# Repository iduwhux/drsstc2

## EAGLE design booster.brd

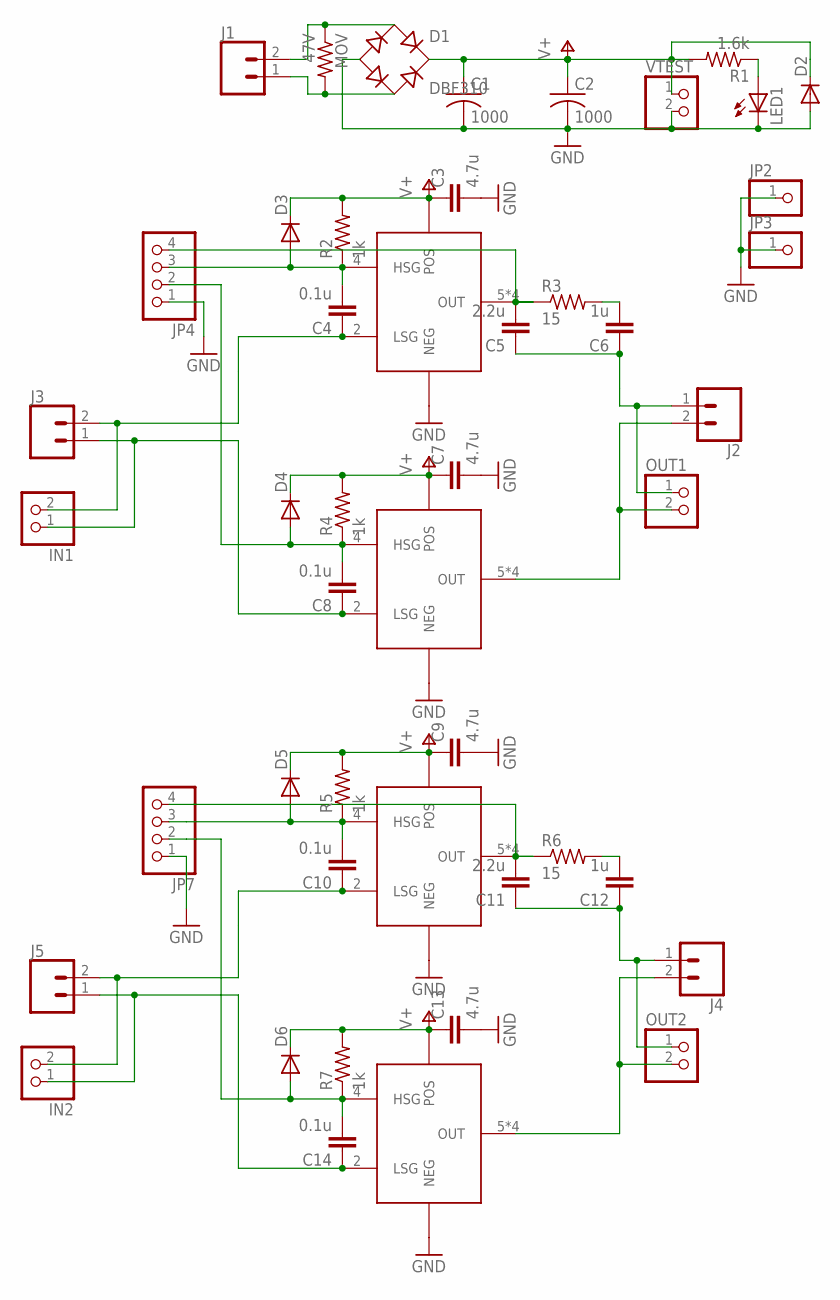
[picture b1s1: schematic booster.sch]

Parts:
C1, C2: 1000; CAPPRD500W65D1250H2500B
C3, C7, C9, C13: 4.7u; C1206
C4, C8, C10, C14: 0.1u; C1206
C5, C11: 2.2u; C1206
C6, C12: 1u; C1206
D1: DBF310; 4-SMD
D2, D3, D4, D5, D6: DIODE-SMB; SMB
IN1, IN2: PINHD-1X2; 1X02
J1, J2, J3, J4, J5: CONN_025MM; SCREWTERMINAL-5MM-2
JP2, JP3: PINHD-1X1; 1X01
JP4, JP7: PINHD-1X4; 1X04
LED1: LED5MM
MOV: 47V; R1206
OUT1, OUT2: PINHD-1X2; 1X02
R1: 1.6k; R2512
R2, R4, R5, R7: 1k; R1206
R3, R6: 15; R1206
U1, U2, U3, U4: SI4554DY; SOIC-8
VTEST: PINHD-1X2; 1X02

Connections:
GND: C1.2, C2.2, C3.2, C7.2, C9.2, C13.2, D1.-, D2.A, JP2.1, JP3.1, JP4.1, JP7.1, LED1.K (C), U1.1 (NEG), U2.1 (NEG), U3.1 (NEG), U4.1 (NEG), VTEST.2
unnamed: LED1.A, R1.1
unnamed: C5.2, JP4.4, R3.1, U1.5 (OUT), U1.6 (OUT), U1.7 (OUT), U1.8 (OUT)
unnamed: D1.~1 (AC1), J1.2, MOV.1
unnamed: C6.2, R3.2
unnamed: C5.1, C6.1, J2.1, OUT1.1
unnamed: J2.2, OUT1.2, U2.5 (OUT), U2.6 (OUT), U2.7 (OUT), U2.8 (OUT)
unnamed: C4.1, IN1.2, J3.2, U1.2 (LSG)
unnamed: C4.2, D3.A, JP4.3, R2.1, U1.4 (HSG)
unnamed: C11.2, JP7.4, R6.1, U3.5 (OUT), U3.6 (OUT), U3.7 (OUT), U3.8 (OUT)
unnamed: C12.2, R6.2
unnamed: C8.1, IN1.1, J3.1, U2.2 (LSG)
unnamed: C8.2, D4.A, JP4.2, R4.1, U2.4 (HSG)
unnamed: C11.1, C12.1, J4.1, OUT2.1
unnamed: C10.1, IN2.2, J5.2, U3.2 (LSG)
unnamed: C10.2, D5.A, JP7.3, R5.1, U3.4 (HSG)
unnamed: C14.1, IN2.1, J5.1, U4.2 (LSG)
unnamed: C14.2, D6.A, JP7.2, R7.1, U4.4 (HSG)
unnamed: J4.2, OUT2.2, U4.5 (OUT), U4.6 (OUT), U4.7 (OUT), U4.8 (OUT)
unnamed: D1.~2 (AC2), J1.1, MOV.2
V+: C1.1, C2.1, C3.1, C7.1, C9.1, C13.1, D1.+, D2.C, D3.C, D4.C, D5.C, D6.C, R1.2, R2.2, R4.2, R5.2, R7.2, U1.3 (POS), U2.3 (POS), U3.3 (POS), U4.3 (POS), VTEST.1

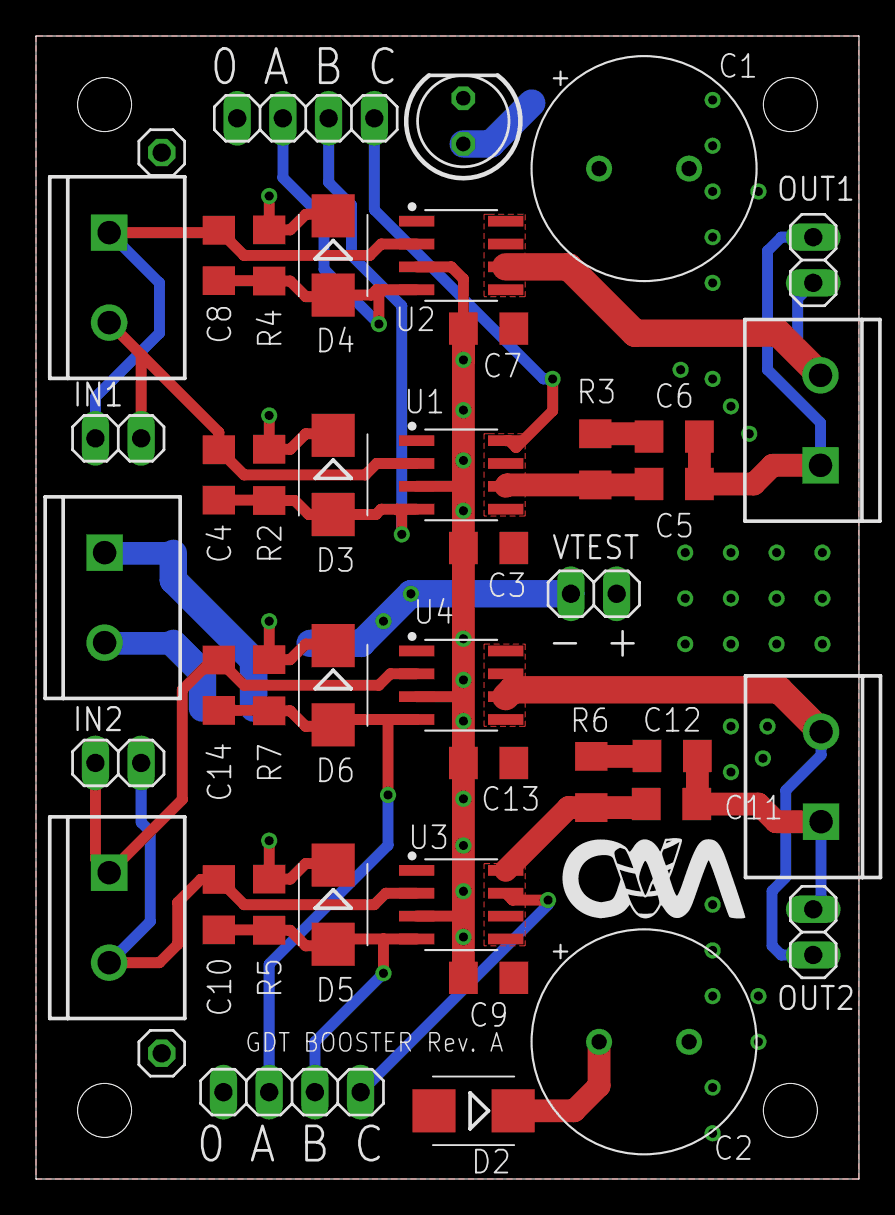
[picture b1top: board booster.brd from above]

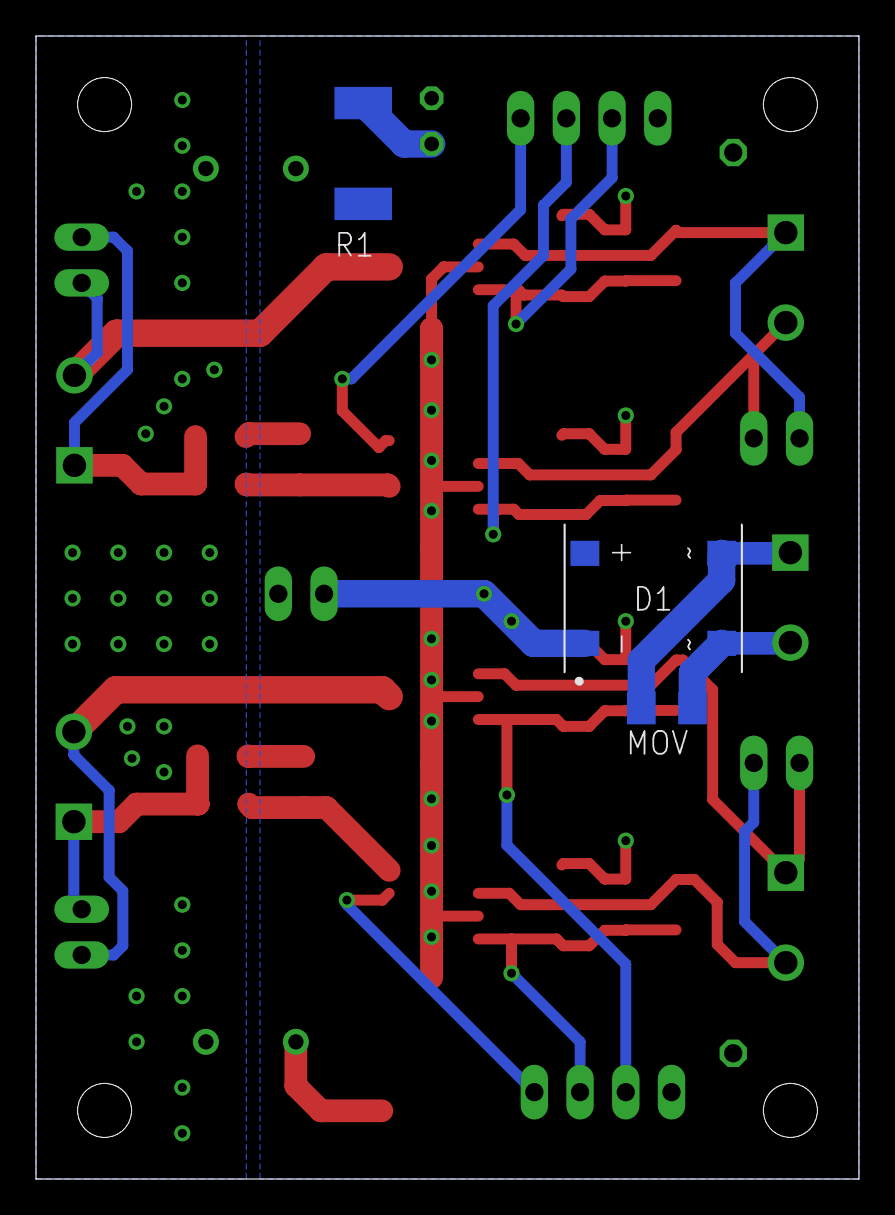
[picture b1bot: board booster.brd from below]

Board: 2 copper layers, 45.7 x 63.5 mm, 47 parts (3 on the bottom side), 21 nets.

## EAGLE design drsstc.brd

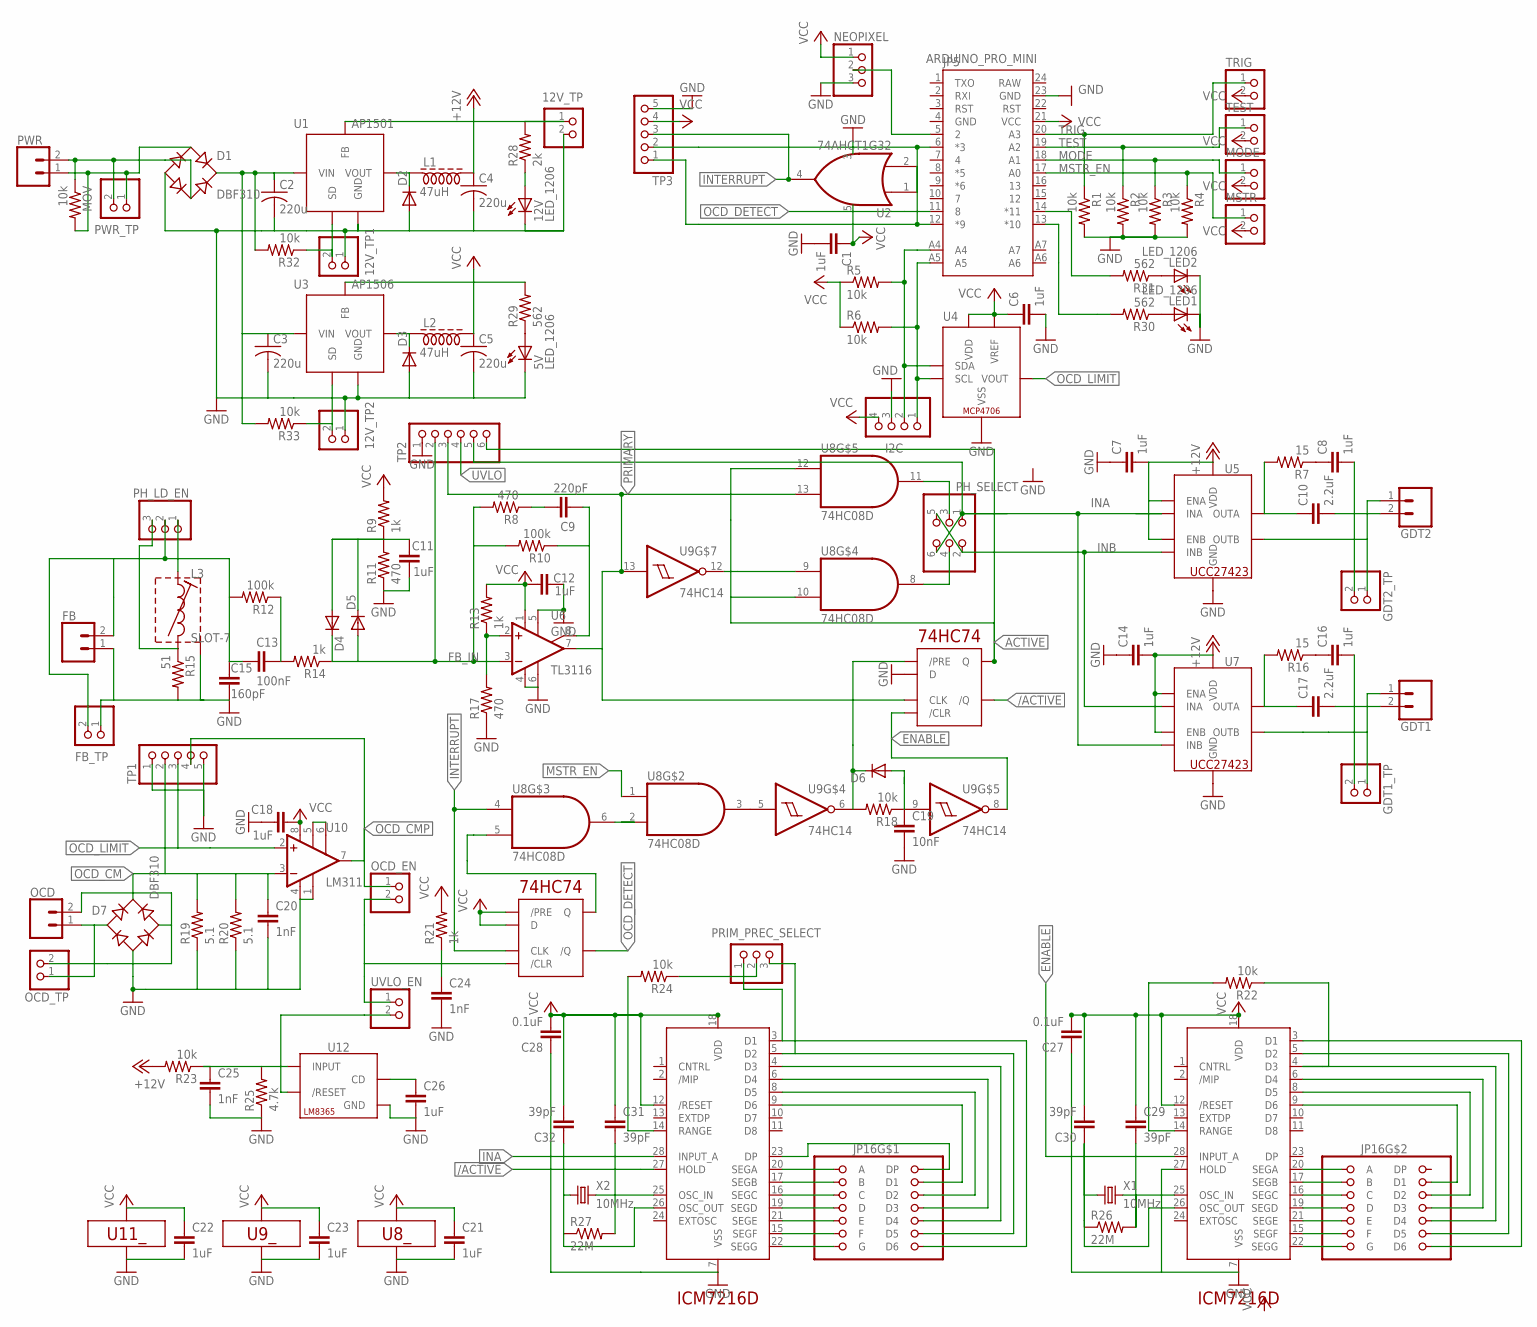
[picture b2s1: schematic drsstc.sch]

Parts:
5V, 12V: LED_1206; CHIPLED_1206
12V_TP, 12V_TP1, 12V_TP2: PINHD-1X2; 1X02
C1, C6, C7, C8, C11, C12, C14, C16, C18, C21, C22, C23, C26: 1uF; C1206
C2, C3, C4, C5: 220u; CAPAE830X1050
C9: 220pF; C1206
C10, C17: 2.2uF; C1206
C13: 100nF; C1206
C15: 160pF; C0402
C19: 10nF; C1206
C20, C24, C25: 1nF; C1206
C27, C28: 0.1uF; C1206
C29, C30, C31, C32: 39pF; C1206
D1, D7: DBF310; 4-SMD
D2, D3, D4, D5, D6: DIODE-SMB; SMB
FB: CONN_025MM; SCREWTERMINAL-5MM-2
FB_TP: PINHD-1X2; 1X02
GDT1, GDT2: CONN_025MM; SCREWTERMINAL-5MM-2
GDT1_TP, GDT2_TP: PINHD-1X2; 1X02
I2C: PINHD-1X4; 1X04
JP5: ARDUINO_PRO_MINI
JP16: LED_HDR; HDRRAR28W64P254_2X14_3606X850X508B
L1, L2: 47uH; RLB9013
L3: SLOT-7
LED1, LED2: LED_1206; CHIPLED_1206
MODE: PINHD-1X2; 1X02
MOV: 10k; R1206
MSTR: PINHD-1X2; 1X02
NEOPIXEL: PINHD-1X3; 1X03
OCD: CONN_025MM; SCREWTERMINAL-5MM-2
OCD_EN: PINHD-1X2; 1X02
OCD_TP: PINHD-1X2; 1X02
PH_LD_EN: PINHD-1X3; 1X03
PH_SELECT: PINHD-2X3; 2X03
PRIM_PREC_SELECT: PINHD-1X3; 1X03
PWR: CONN_025MM; SCREWTERMINAL-5MM-2
PWR_TP: PINHD-1X2; 1X02
R1, R2, R3, R4, R5, R6, R18, R22, R23, R24, R32, R33: 10k; R1206
R7, R16: 15; R1206
R8, R11, R17: 470; R1206
R9, R13, R14, R21: 1k; R1206
R10, R12: 100k; R1206
R15: 51; RESAD1560W80L1200D400B
R19, R20: 5.1; R1206
R25: 4.7k; R1206
R26, R27: 22M; R1206
R28: 2k; R1206
R29, R30, R31: 562; R1206
TEST: PINHD-1X2; 1X02
TP1, TP3: PINHD-1X5; 1X05
TP2: PINHD-1X6; 1X06
TRIG: PINHD-1X2; 1X02
U1: AP1501; TO-263-5
U2: 74AHCT1G32; SOT353
U3: AP1506; TO-263-5
U4: MCP4706; SOT-23-6
U5, U7: UCC27423; SOIC-8
U6: TL3116; SOIC-8
U8: 74HC08D; SOIC-14
U9: 74HC14; SOIC-14
U10: LM311; SOIC-8
U11: 74HC74; SOIC-14
U12: LM8365; SOT-23-5
U13, U14: ICM7216D; DIP1524W55P254L3740H635Q28B
UVLO_EN: PINHD-1X2; 1X02
X1, X2: 10MHz; XTAL

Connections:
+12V: 12V_TP.1, C4.1, C7.2, C14.2, L1.P$2 (2), R23.2, R28.2, U1.4 (FB), U5.1 (ENA), U5.6 (VDD), U5.8 (ENB), U7.1 (ENA), U7.6 (VDD), U7.8 (ENB)
/ACTIVE: U11.8 (/Q), U14.27 (HOLD)
ACTIVE: TP2.6, U8.10 (I1), U8.12 (I0), U11.9 (Q)
D1: JP16.1 (D6), PRIM_PREC_SELECT.1, U14.3 (D1)
D2: JP16.2 (D5), PRIM_PREC_SELECT.3, U14.5 (D2)
D4: JP16.3 (D4), U14.4 (D3)
ENABLE: U9.8 (O), U11.13 (/CLR), U13.28 (INPUT_A)
FB_IN: D4.C, D5.A, R8.2, R10.2, R14.1, TP2.2, U6.3 (-IN)
GDT1_1: GDT1.1, GDT1_TP.1, U7.5 (OUTB)
GDT1_2: C16.2, C17.2, GDT1.2, GDT1_TP.2
GDT2_1: GDT2.1, GDT2_TP.1, U5.5 (OUTB)
GDT2_2: C8.2, C10.2, GDT2.2, GDT2_TP.2
GND: 5V.C, 12V.C, 12V_TP.2, 12V_TP1.1, 12V_TP2.1, C1.2, C2.2, C3.2, C4.2, C5.2, C6.2, C7.1, C11.1, C12.2, C14.1, C15.2, C18.1, C19.2, C20.2, C21.2, C22.2, C23.2, C24.2, C25.2, C26.2, C27.1, C28.1, D1.-, D2.A, D3.A, D7.-, FB.1, FB_TP.1, I2C.3, JP5.4 (GND), JP5.23 (GND), L3.SHIELD_1 (SHIELD), L3.SHIELD_2 (SHIELD), LED1.C, LED2.C, NEOPIXEL.3, R1.2, R2.2, R3.2, R4.2, R11.1, R15.2, R17.1, R19.1, R20.1, R25.1, TP1.1, TP1.5, TP2.1, TP3.5, U1.3 (GND), U1.6 (GND), U2.3 (GND), U3.3 (GND), U3.6 (GND), U4.2 (VSS), U5.3 (GND), U6.4 (VCC-), U6.5 (LATCH_EN), U6.6 (GND), U7.3 (GND), U8.7 (GND), U9.7 (GND), U10.1 (GND), U10.4 (VCC-), U11.7 (GND), U11.12 (D), U12.3 (GND), U13.7 (VSS), U13.27 (HOLD), U14.7 (VSS)
INA: PH_SELECT.1, PH_SELECT.6, TP2.5, U5.2 (INA), U7.4 (INB), U14.28 (INPUT_A)
INB: PH_SELECT.2, PH_SELECT.5, U5.4 (INB), U7.2 (INA)
INTERRUPT: TP3.3, U2.4 (O), U8.4 (I0), U11.3 (CLK)
MODE: JP5.18 (A1), MODE.1, R3.1
MSTR_EN: JP5.17 (A0), MSTR.1, R4.1, U8.1 (I0)
unnamed: D1.~2 (AC2), MOV.1, PWR.2, PWR_TP.2
unnamed: D7.~1 (AC1), OCD.1, OCD_TP.1
unnamed: JP16.13 (A), U13.20 (SEGA)
unnamed: C26.1, U12.5 (CD)
unnamed: C24.1, OCD_EN.2, R21.1, U11.1 (/CLR), UVLO_EN.1
unnamed: C25.1, R23.1, R25.2, U12.2 (INPUT)
unnamed: U10.5 (BAL), U10.6 (BAL/S)
unnamed: C19.1, D6.A, R18.1, U9.9 (I)
unnamed: U8.9 (I0), U9.12 (O)
unnamed: U8.5 (I1), U11.5 (Q)
unnamed: U8.3 (O), U9.5 (I)
unnamed: D6.C, R18.2, U9.6 (O), U11.10 (/PRE)
unnamed: JP5.5 (2), NEOPIXEL.2
unnamed: D7.~2 (AC2), OCD.2, OCD_TP.2
unnamed: U8.2 (I1), U8.6 (O)
unnamed: PH_SELECT.4, U8.8 (O)
unnamed: PH_SELECT.3, U8.11 (O)
unnamed: 12V.A, R28.1
unnamed: JP5.6 (*3), TP3.2, U2.1 (I0)
unnamed: C13.2, C15.1, FB.2, FB_TP.2, PH_LD_EN.2, R12.2
unnamed: L3.START (2), PH_LD_EN.3, R15.1
unnamed: L3.FINISH (1), PH_LD_EN.1
unnamed: C9.2, R10.1, U6.8 (/Q)
unnamed: C9.1, R8.1
unnamed: C11.2, D4.A, D5.C, R9.1, R11.2
unnamed: R13.1, R17.2, U6.2 (+IN)
unnamed: C13.1, R12.1, R14.2
unnamed: D1.~1 (AC1), MOV.2, PWR.1, PWR_TP.1
unnamed: C8.1, R7.1
unnamed: C10.1, R7.2, U5.7 (OUTA)
unnamed: 5V.A, R29.1
unnamed: LED2.A, R31.1
unnamed: C16.1, R16.1
unnamed: C17.1, R16.2, U7.7 (OUTA)
unnamed: LED1.A, R30.1
unnamed: 12V_TP1.2, R32.1, U1.5 (SD)
unnamed: JP5.12 (*9), TP3.1, U2.2 (I1)
unnamed: C2.1, C3.1, D1.+, R32.2, R33.2, U1.1 (VIN), U3.1 (VIN)
unnamed: D3.C, L2.P$1 (1), U3.2 (VOUT)
unnamed: JP5.13 (*10), R30.2
unnamed: D2.C, L1.P$1 (1), U1.2 (VOUT)
unnamed: C32.1, R27.1, U14.26 (OSC_OUT), X2.P$1 (1)
unnamed: JP5.14 (*11), R31.2
unnamed: R24.2, U14.14 (RANGE)
unnamed: C31.2, R27.2, U14.25 (OSC_IN), X2.P$2 (2)
unnamed: 12V_TP2.2, R33.1, U3.5 (SD)
unnamed: JP16.12 (B), U13.17 (SEGB)
unnamed: JP16.20 (C), U13.16 (SEGC)
unnamed: JP16.19 (D), U13.19 (SEGD)
unnamed: JP16.18 (E), U13.21 (SEGE)
unnamed: R22.2, U13.14 (RANGE)
unnamed: C29.2, R26.2, U13.25 (OSC_IN), X1.P$2 (2)
unnamed: C30.1, R26.1, U13.26 (OSC_OUT), X1.P$1 (1)
unnamed: JP16.14 (F), U13.15 (SEGF)
unnamed: JP16.11 (G), U13.22 (SEGG)
unnamed: JP16.15 (D1), U13.9 (D6)
unnamed: JP16.16 (D2), U13.8 (D5)
unnamed: JP16.17 (D3), U13.6 (D4)
unnamed: JP16.9 (D5), U13.5 (D2)
unnamed: JP16.8 (D6), U13.3 (D1)
unnamed: JP16.6 (A), U14.20 (SEGA)
unnamed: JP16.5 (B), U14.17 (SEGB)
unnamed: JP16.27 (C), U14.16 (SEGC)
unnamed: JP16.26 (D), U14.19 (SEGD)
unnamed: JP16.25 (E), U14.21 (SEGE)
unnamed: JP16.7 (F), U14.15 (SEGF)
unnamed: JP16.4 (G), U14.22 (SEGG)
unnamed: JP16.28 (DP), U14.23 (DP)
unnamed: JP16.22 (D1), U14.9 (D6)
unnamed: PRIM_PREC_SELECT.2, R24.1
unnamed: JP16.10 (D4), R22.1, U13.4 (D3)
unnamed: JP16.24 (D3), U14.6 (D4)
unnamed: JP16.23 (D2), U14.8 (D5)
OCD_CM: C20.1, D7.+, R19.2, R20.2, TP1.2, U10.3 (IN-)
OCD_CMP: OCD_EN.1, TP1.4, U10.7 (OUT)
OCD_DETECT: JP5.11 (8), U11.6 (/Q)
OCD_LIMIT: TP1.3, U4.1 (VOUT), U10.2 (IN+)
PRIMARY: TP2.3, U6.7 (Q), U8.13 (I1), U9.13 (I), U11.11 (CLK)
RAW: JP5.24 (RAW)
SCL: I2C.1, JP5.A5, R6.2, U4.5 (SCL)
SDA: I2C.2, JP5.A4, R5.2, U4.4 (SDA)
TEST: JP5.19 (A2), R2.1, TEST.1
TRIG: JP5.20 (A3), R1.1, TRIG.1
UVLO: TP2.4, U12.1 (/RESET), UVLO_EN.2
VCC: C1.1, C5.1, C6.1, C12.1, C18.2, C21.1, C22.1, C23.1, C27.2, C28.2, C29.1, C30.2, C31.1, C32.2, I2C.4, JP5.21 (VCC), L2.P$2 (2), MODE.2, MSTR.2, NEOPIXEL.1, R5.1, R6.1, R9.2, R13.2, R21.2, R29.2, TEST.2, TP3.4, TRIG.2, U2.5 (VCC), U3.4 (FB), U4.3 (VDD), U4.6 (VREF), U6.1 (VCC+), U8.14 (VCC), U9.14 (VCC), U10.8 (VCC+), U11.2 (D), U11.4 (/PRE), U11.14 (VCC), U13.12 (/RESET), U13.18 (VDD), U14.12 (/RESET), U14.18 (VDD)

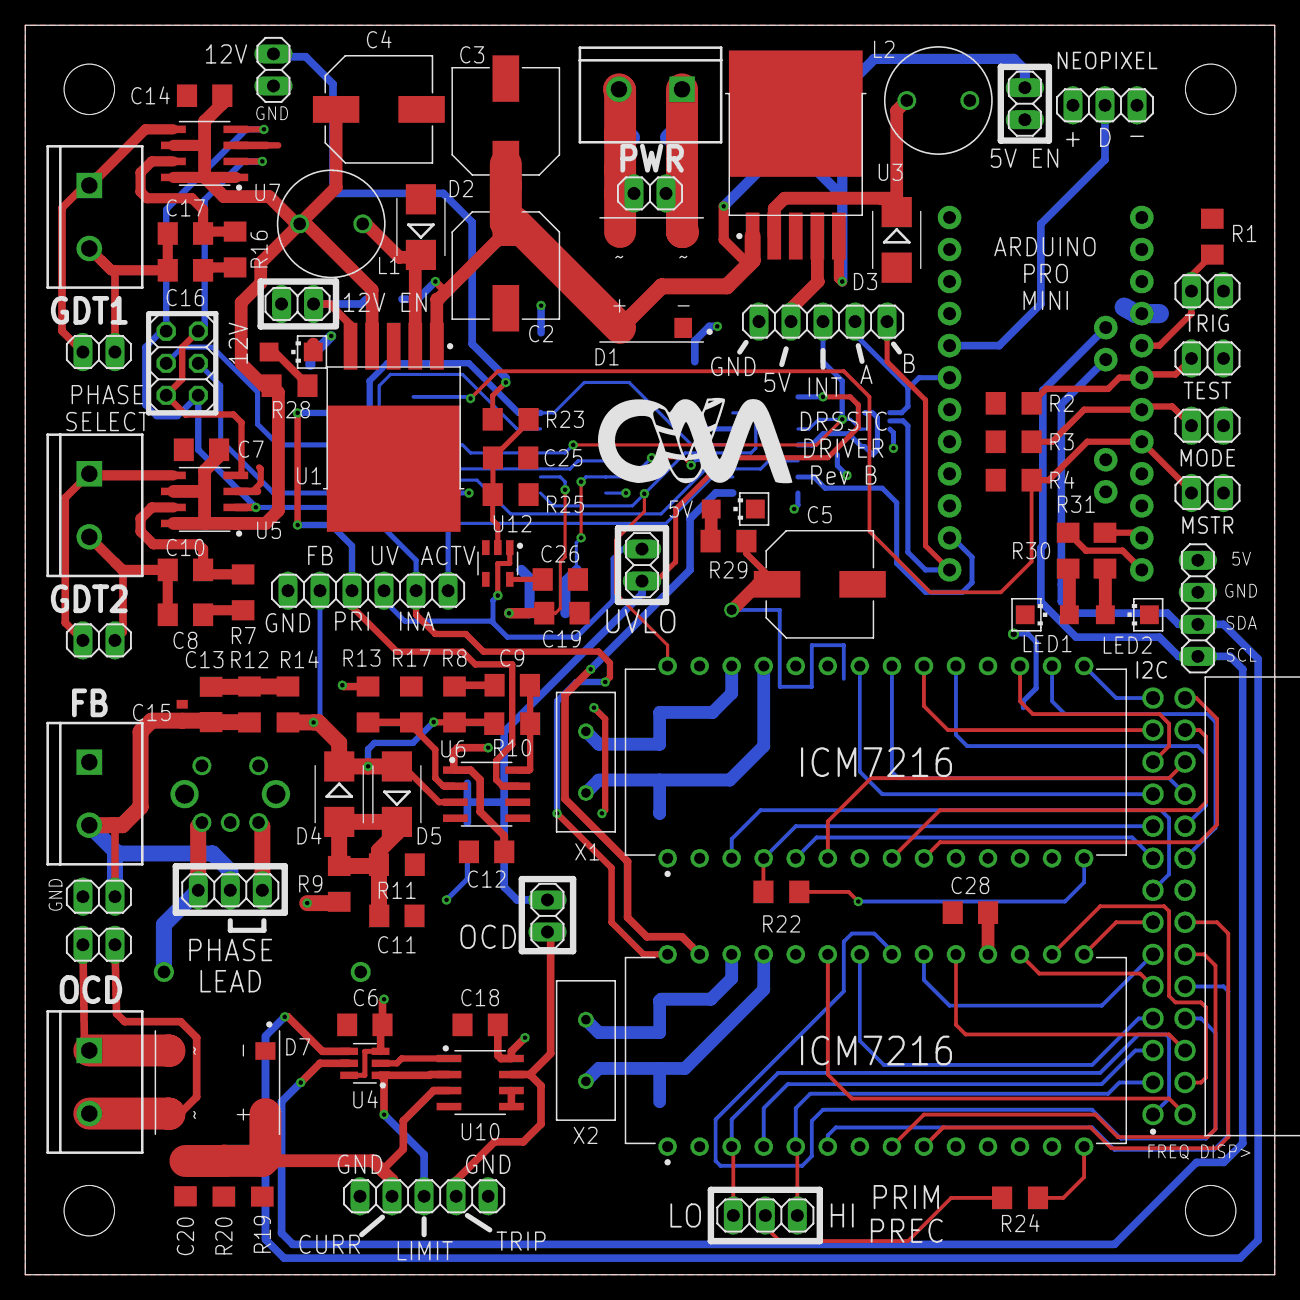
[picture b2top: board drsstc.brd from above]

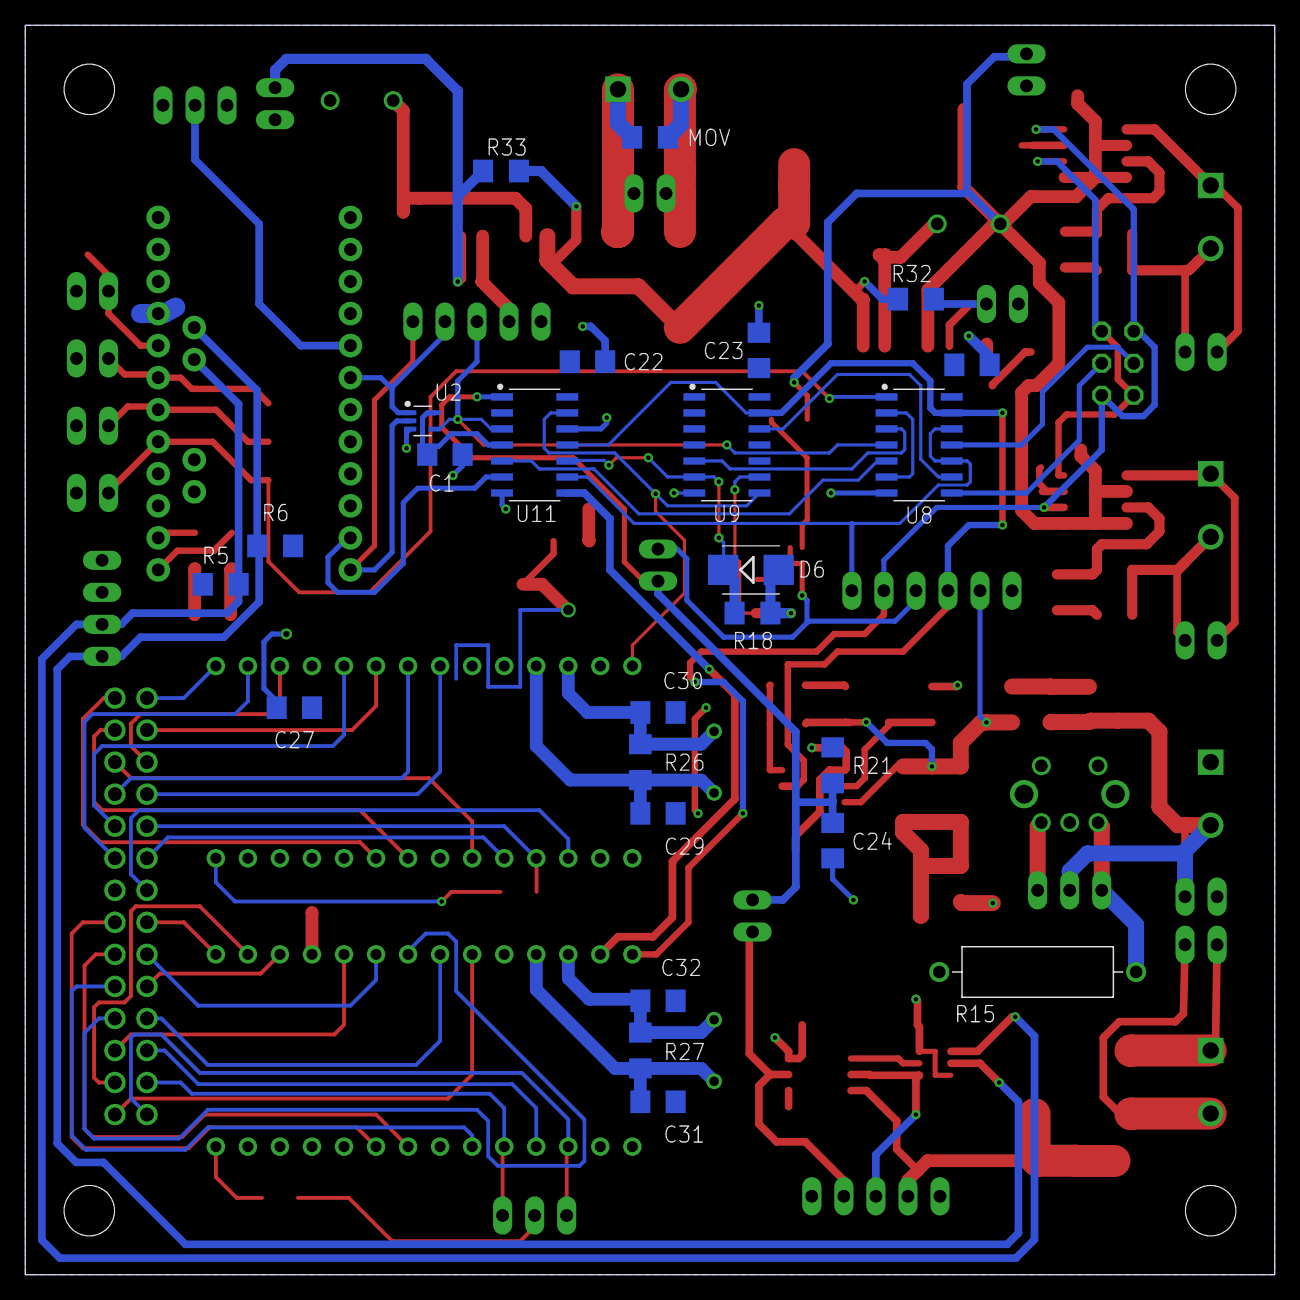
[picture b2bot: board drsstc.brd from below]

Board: 2 copper layers, 99.1 x 99.1 mm, 125 parts (25 on the bottom side), 102 nets.

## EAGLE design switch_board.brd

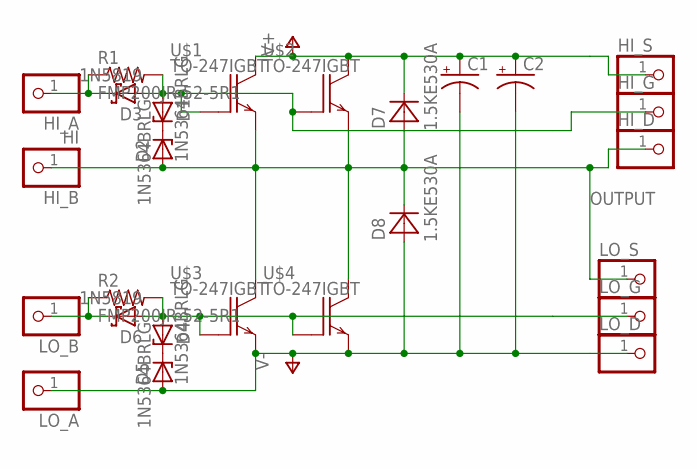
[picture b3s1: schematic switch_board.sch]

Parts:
C1, C2: CPOL-USTAP5-45; TAP5-45
D1, D2, D4, D5: 1N5364BRLG; DIOAD1576W109L863D349B
D3, D6: 1N5819; DIOAD1138W86L470D235B
D7, D8: 1.5KE530A; DIOAD1631W107L835D505B
HI_A: PINHD-1X1; 1X01
HI_B: HI; 1X01
HI_D: PINHD-1X1; 1X01
HI_G: PINHD-1X1; 1X01
HI_S: PINHD-1X1; 1X01
LO_A: PINHD-1X1; 1X01
LO_B: PINHD-1X1; 1X01
LO_D: PINHD-1X1; 1X01
LO_G: PINHD-1X1; 1X01
LO_S: PINHD-1X1; 1X01
R1, R2: FMP200JR-52-5R1; RESAD1260W55L900D390B
U$1, U$2, U$3, U$4: TO-247IGBT; TO-247

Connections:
unnamed: D1.2 (A), D3.2 (A), HI_G.1, R1.2, U$1.G, U$2.G
unnamed: D1.1 (C), D2.1 (C)
unnamed: D3.1 (C), HI_A.1, R1.1
unnamed: D4.2 (A), D6.2 (A), LO_G.1, R2.2, U$3.G, U$4.G
unnamed: D4.1 (C), D5.1 (C)
unnamed: D6.1 (C), LO_B.1, R2.1
OUTPUT: D2.2 (A), D7.2 (A), D8.1 (C), HI_B.1, HI_D.1, LO_S.1, U$1.E, U$2.E, U$3.C, U$4.C
V+: C1.+, C2.+, D7.1 (C), HI_S.1, U$1.C, U$2.C
V-: C1.-, C2.-, D5.2 (A), D8.2 (A), LO_A.1, LO_D.1, U$3.E, U$4.E

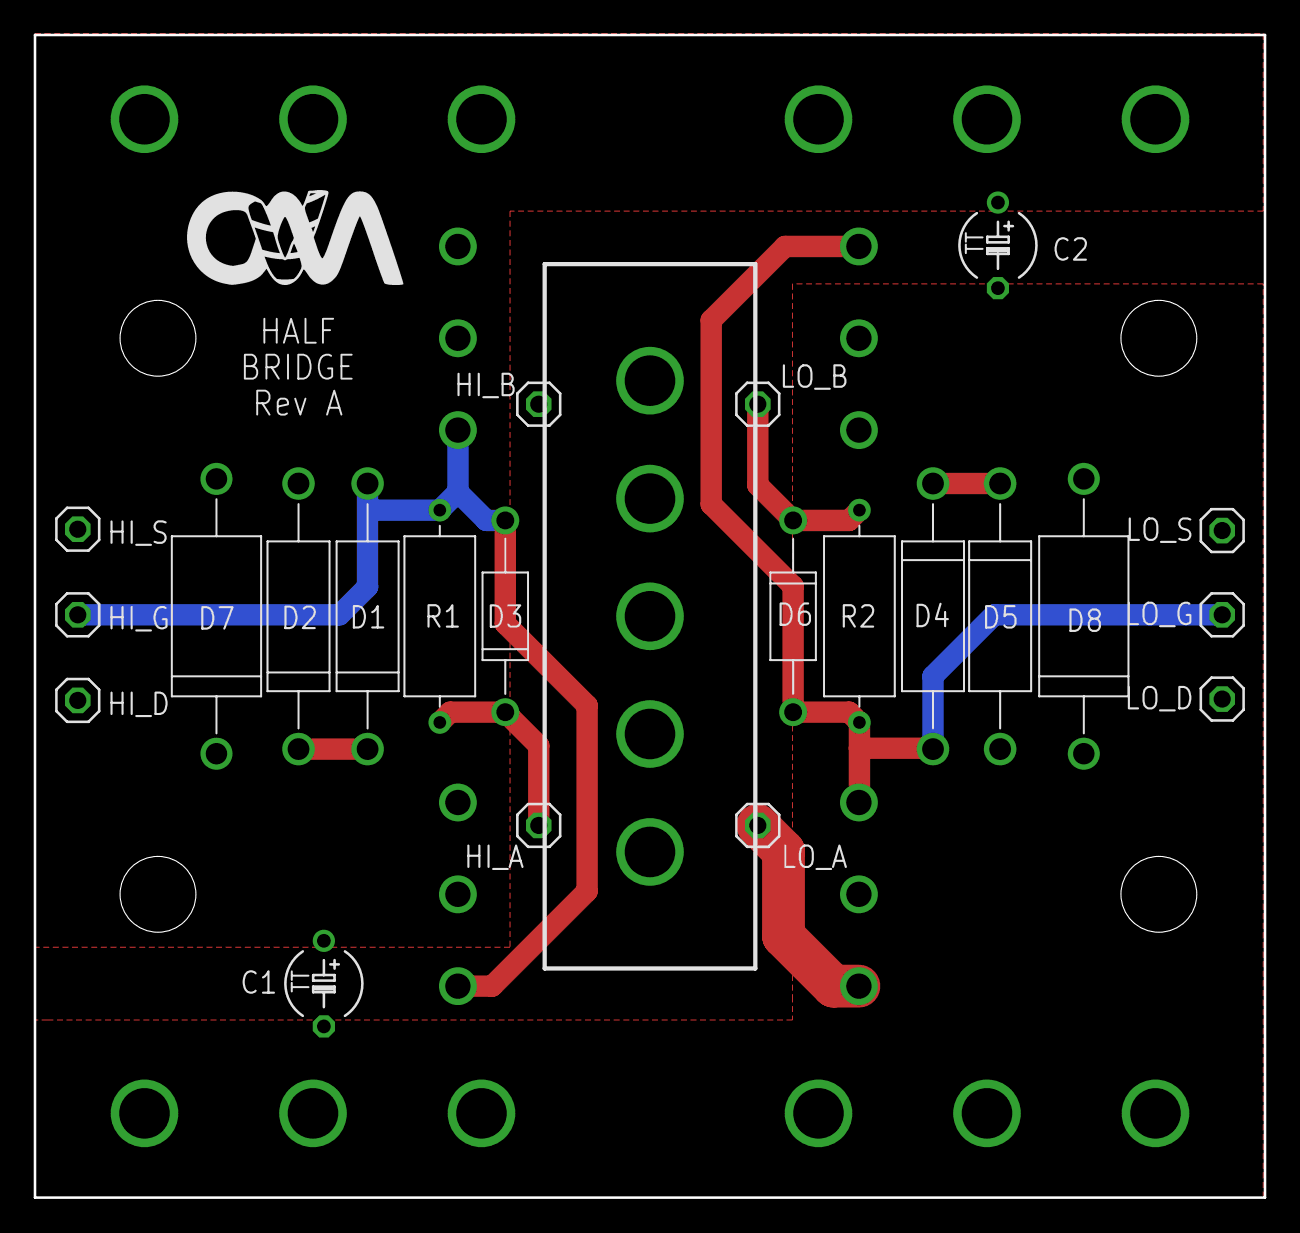
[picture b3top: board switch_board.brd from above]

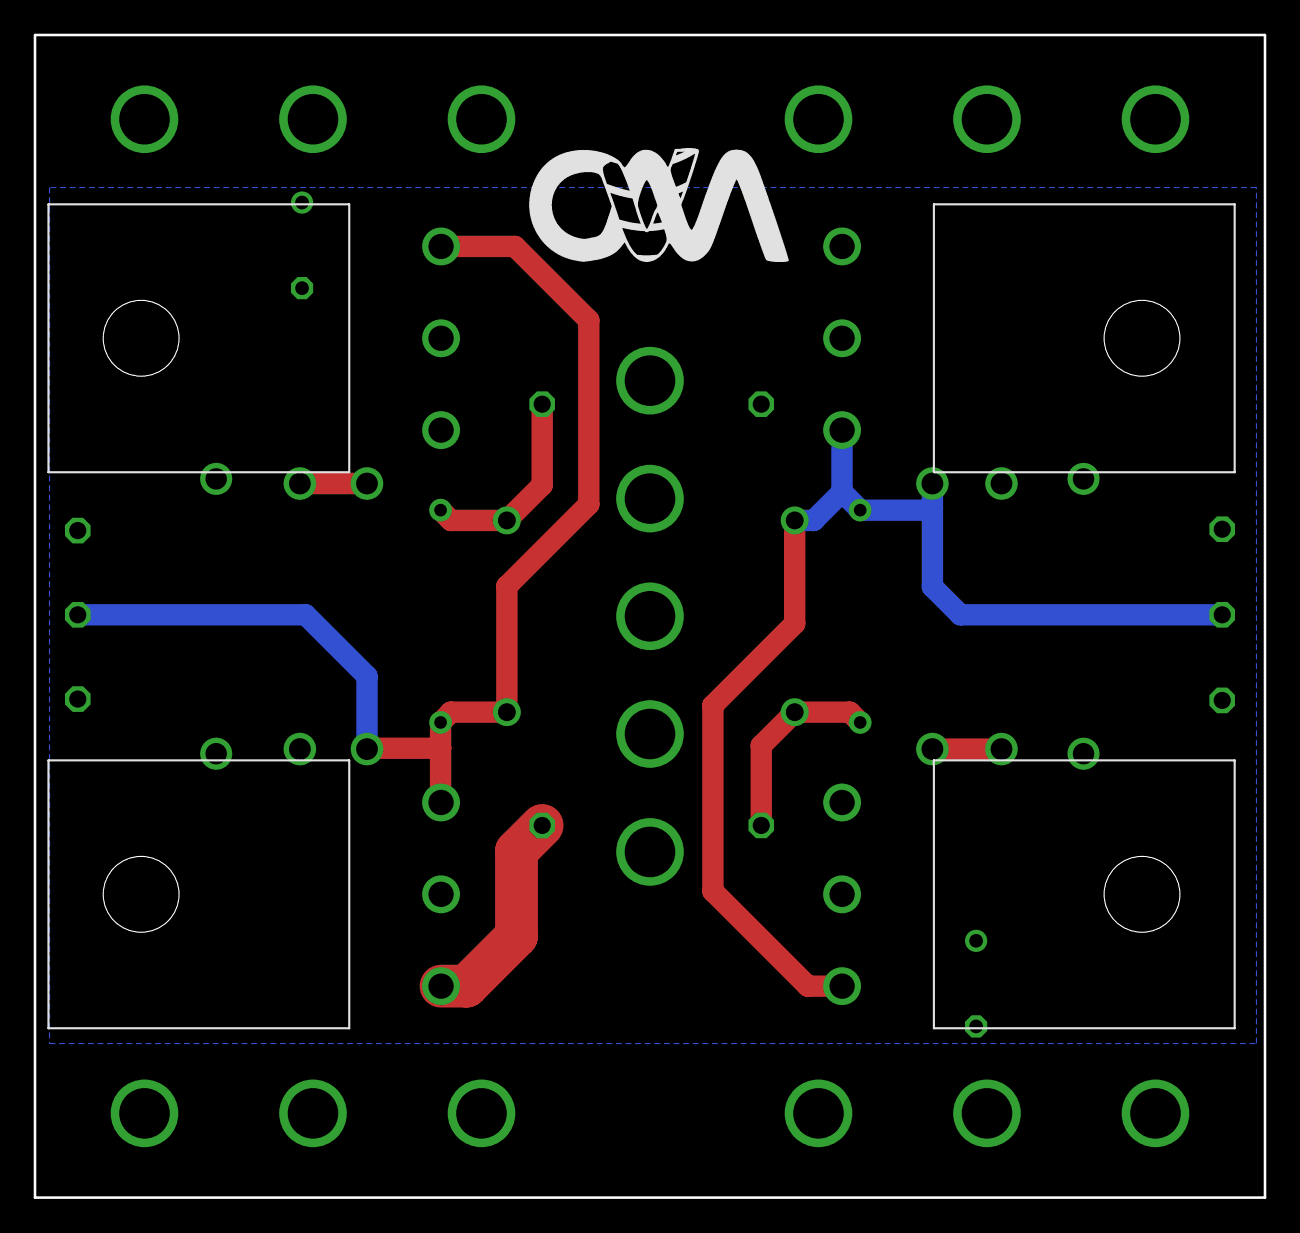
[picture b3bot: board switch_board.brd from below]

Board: 2 copper layers, 73.0 x 69.0 mm, 26 parts (4 on the bottom side), 9 nets.

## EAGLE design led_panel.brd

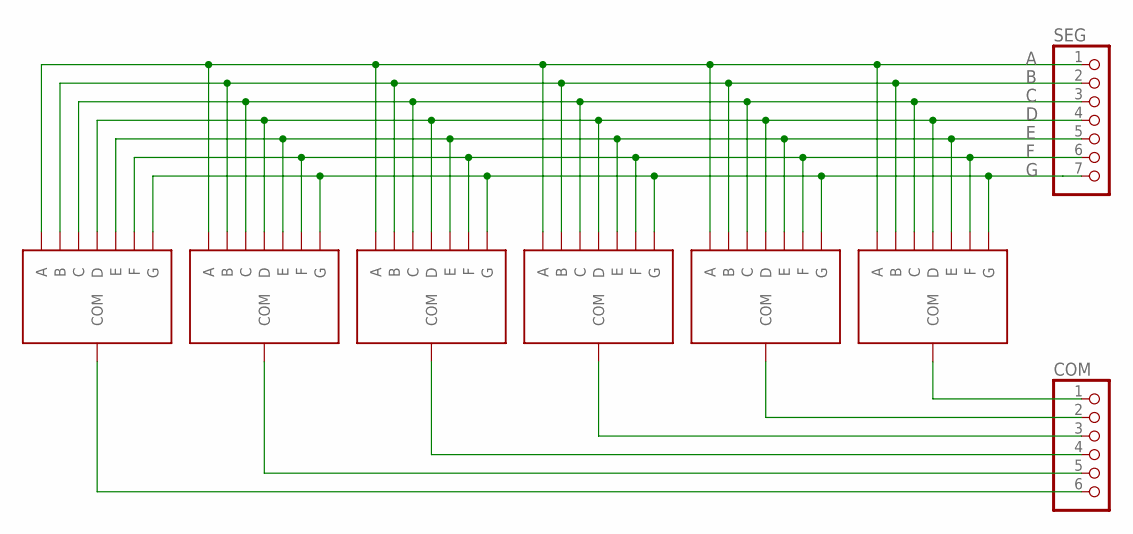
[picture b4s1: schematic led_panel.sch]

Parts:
COM: PINHD-1X6; 1X06
SEG: PINHD-1X7; 1X07
U$1, U$2, U$3, U$4, U$5, U$6: 7SEGMENTLED

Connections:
A: SEG.1, U$1.P$4 (A), U$2.P$4 (A), U$3.P$4 (A), U$4.P$4 (A), U$5.P$4 (A), U$6.P$4 (A)
B: SEG.2, U$1.P$5 (B), U$2.P$5 (B), U$3.P$5 (B), U$4.P$5 (B), U$5.P$5 (B), U$6.P$5 (B)
C: SEG.3, U$1.P$9 (C), U$2.P$9 (C), U$3.P$9 (C), U$4.P$9 (C), U$5.P$9 (C), U$6.P$9 (C)
D: SEG.4, U$1.P$7 (D), U$2.P$7 (D), U$3.P$7 (D), U$4.P$7 (D), U$5.P$7 (D), U$6.P$7 (D)
E: SEG.5, U$1.P$6 (E), U$2.P$6 (E), U$3.P$6 (E), U$4.P$6 (E), U$5.P$6 (E), U$6.P$6 (E)
F: SEG.6, U$1.P$2 (F), U$2.P$2 (F), U$3.P$2 (F), U$4.P$2 (F), U$5.P$2 (F), U$6.P$2 (F)
G: SEG.7, U$1.P$1 (G), U$2.P$1 (G), U$3.P$1 (G), U$4.P$1 (G), U$5.P$1 (G), U$6.P$1 (G)
unnamed: COM.6, U$1.P$3 (COM), U$1.P$8 (COM), U$1.P$10 (COM)
unnamed: COM.5, U$2.P$3 (COM), U$2.P$8 (COM), U$2.P$10 (COM)
unnamed: COM.4, U$3.P$3 (COM), U$3.P$8 (COM), U$3.P$10 (COM)
unnamed: COM.3, U$4.P$3 (COM), U$4.P$8 (COM), U$4.P$10 (COM)
unnamed: COM.2, U$5.P$3 (COM), U$5.P$8 (COM), U$5.P$10 (COM)
unnamed: COM.1, U$6.P$3 (COM), U$6.P$8 (COM), U$6.P$10 (COM)

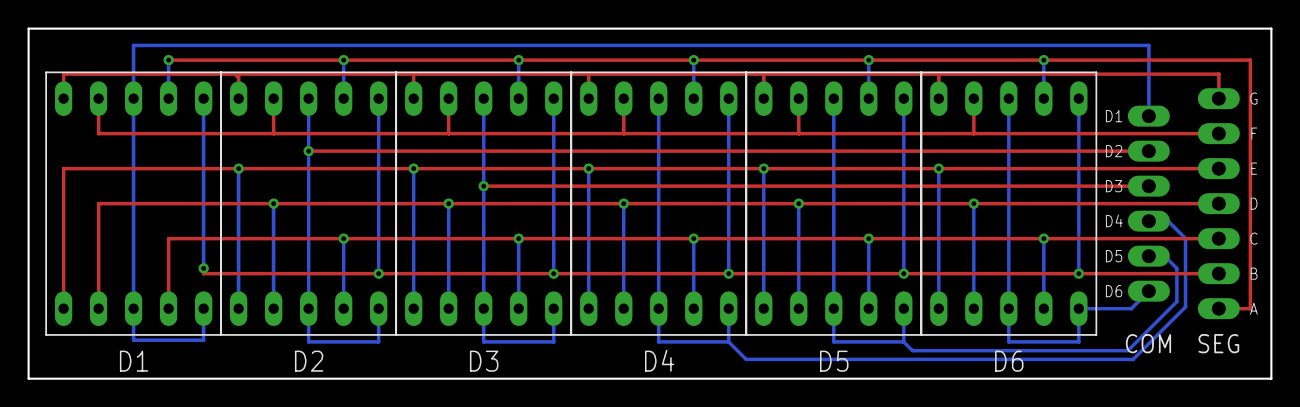
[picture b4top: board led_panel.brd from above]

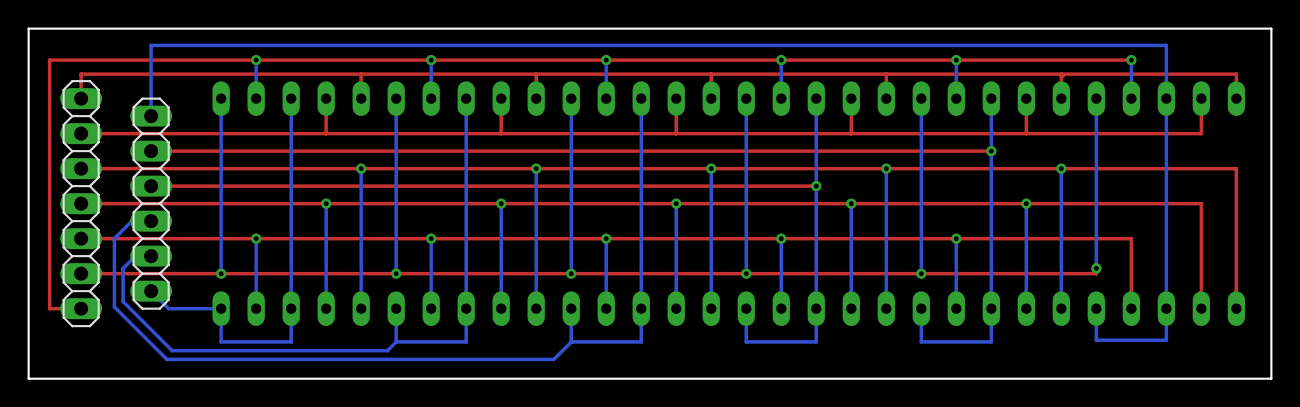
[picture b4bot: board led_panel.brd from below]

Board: 2 copper layers, 90.2 x 25.4 mm, 8 parts (2 on the bottom side), 13 nets.

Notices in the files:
parts and their libraries:
SparkFun-Connectors: Licensing: Creative Commons ShareAlike 4.0 International - https://creativecommons.org/licenses/by-sa/4.0
